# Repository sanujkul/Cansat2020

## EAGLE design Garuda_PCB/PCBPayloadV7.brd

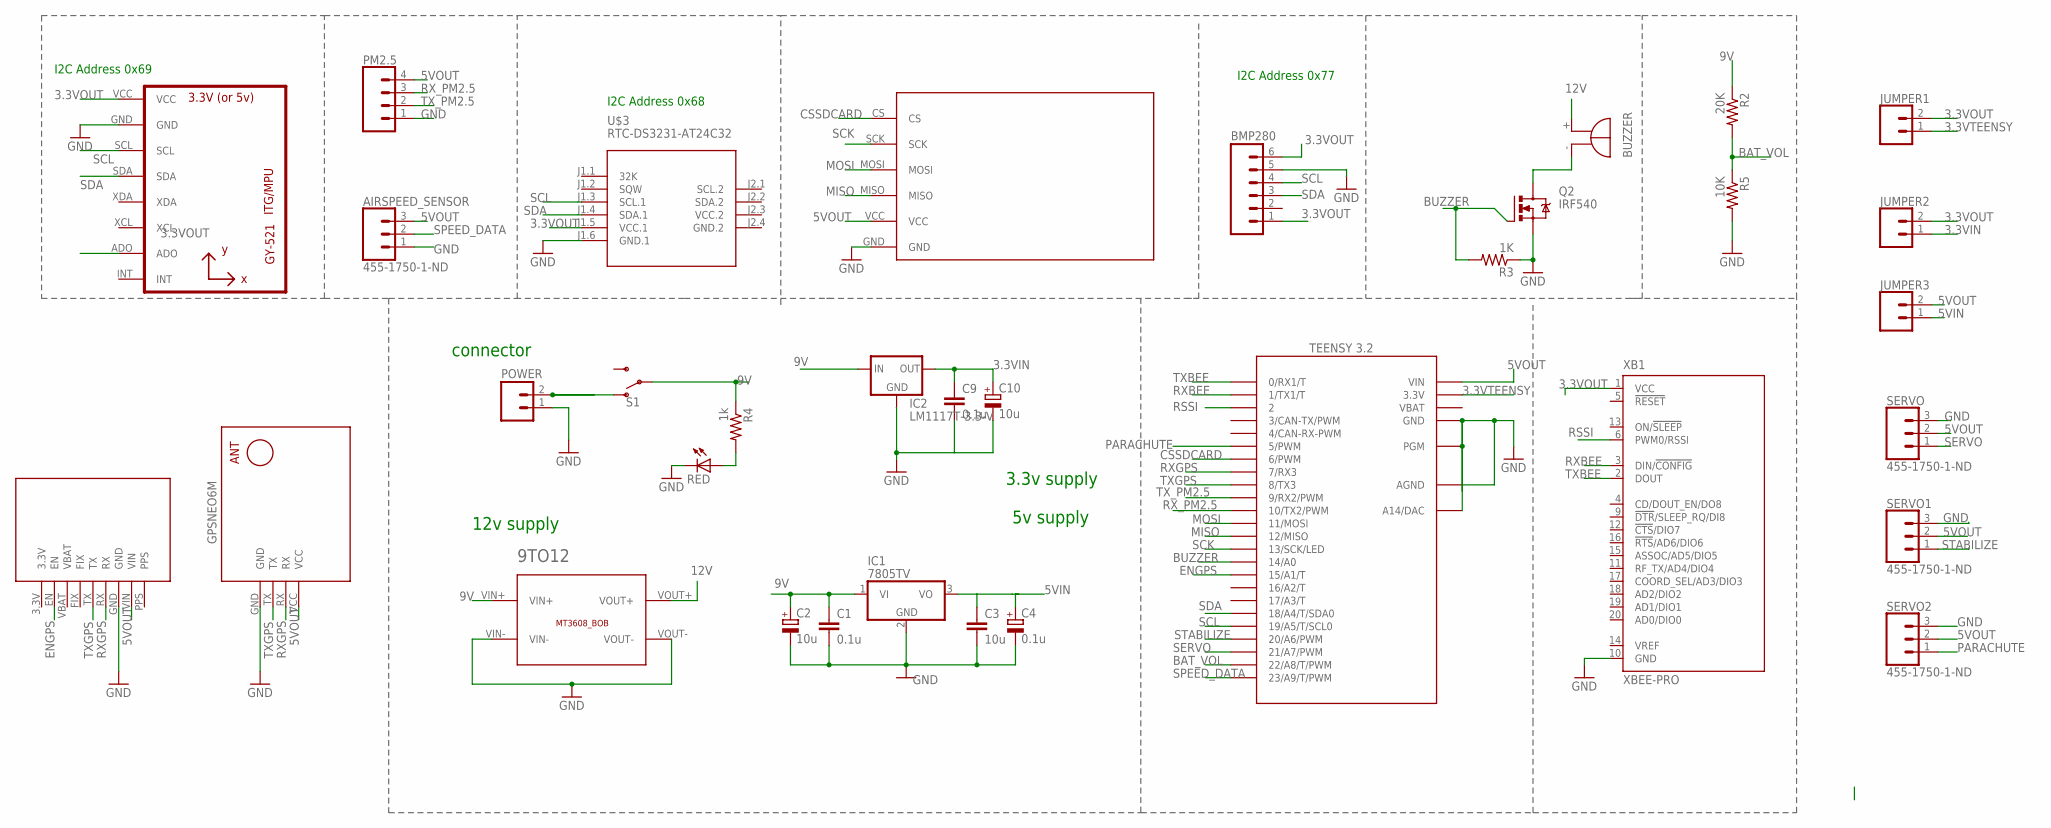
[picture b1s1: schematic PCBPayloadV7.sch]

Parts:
9TO12: BREAKOUTS_MT3608_BOB
AIRSPEED_SENSOR: 455-1750-1-ND; 1X03
BMP280: M06; 06P
C1, C9: 0.1u; C025-025X050
C2, C10: 10u; E2,5-6
C3: 10u; C025-025X050
C4: 0.1u; E2,5-6
IC1: 7805TV; TO220V
IC2: LM1117T-3.3-V; TO220V
JUMPER1, JUMPER2, JUMPER3: CONN_02; 1X02
PM2.5: CONN_04; 1X04
POWER: CEDT_JANUARY_2015_V5_M02; CEDT_JANUARY_2015_V5_02P
Q2: IRF540; TO220BV
R2: 20K; 0204/7
R3: 1K; 0204/7
R4: 1k; 0204/7
R5: 10K; 0204/7
RED: red; LED3MM
S1: SWITCH-SPDT-PTH-11.6X4.0MM; SWITCH_SPDT_PTH_11.6X4.0MM
SERVO, SERVO1, SERVO2: 455-1750-1-ND; 1X03
SG1: BUZZER_EB2209A
U1: GY-521MPU6050; GY-521
U$1: GPS-RECEIVER-NEO6M
U$2: TEENSY_3.1-3.2_OUTER_ROW; TEENSY_3.0-3.2&LC_OUTER_ROW
U$3: RTC-DS3231-AT24C32
U$4: ADAFRUIT_GPS
U$5: SDCARD; M0SDCARDMODULE
XB1: XBEE-PRO

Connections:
3.3VIN: C9.1, C10.+, IC2.2 (OUT), JUMPER2.1
3.3VOUT: BMP280.1, BMP280.6, JUMPER1.2, JUMPER2.2, U1.ADO, U1.VCC, U$3.J1.5 (VCC.1), XB1.1 (VCC)
3.3VTEENSY: JUMPER1.1, U$2.3.3V, U$2.3.3V1 (3.3V)
5VIN: C3.1, C4.+, IC1.3 (VO), JUMPER3.1
5VOUT: AIRSPEED_SENSOR.3, JUMPER3.2, PM2.5.4, SERVO.2, SERVO1.2, SERVO2.2, U$1.VCC, U$2.VIN, U$4.VIN, U$5.VCC
9V: 9TO12.VIN+, C1.1, C2.+, IC1.1 (VI), IC2.3 (IN), R2.1, R4.1, S1.2
12V: 9TO12.VOUT+, SG1.+
BAT_VOL: R2.2, R5.1, U$2.22/A8 (22/A8/T/PWM)
BUZZER: Q2.G, R3.2, U$2.14/A0
CSSDCARD: U$2.6 (6/PWM), U$5.CS
ENGPS: U$2.15/A1 (15/A1/T), U$4.EN
GND: 9TO12.VIN-, 9TO12.VOUT-, AIRSPEED_SENSOR.1, BMP280.5, C1.2, C2.-, C3.2, C4.-, C9.2, C10.-, IC1.2 (GND), IC2.1 (GND), PM2.5.1, POWER.1, Q2.S, R3.1, R5.2, RED.K (C), SERVO.3, SERVO1.3, SERVO2.3, U1.GND, U$1.GND, U$2.AGND, U$2.GND, U$2.GND1 (GND), U$2.PGM, U$2.RESET/DAC (A14/DAC), U$3.J1.6 (GND.1), U$4.GND, U$5.GND, XB1.10 (GND)
GND.2: U$3.J2.4 (GND.2)
MISO: U$2.12 (12/MISO), U$5.MISO
MOSI: U$2.11 (11/MOSI), U$5.MOSI
unnamed: POWER.2, S1.1 (O)
unnamed: R4.2, RED.A
unnamed: Q2.D, SG1.-
PARACHUTE: SERVO2.1, U$2.5 (5/PWM)
RSSI: U$2.2, XB1.6 (PWM0/RSSI)
RXBEE: U$2.1 (1/TX1/T), XB1.3 (DIN/!CONFIG)
RXGPS: U$1.RX, U$2.7 (7/RX3), U$4.RX
RX_PM2.5: PM2.5.3, U$2.10 (10/TX2/PWM)
SCK: U$2.13 (13/SCK/LED), U$5.SCK
SCL: BMP280.4, U1.SCL, U$2.19/A5 (19/A5/T/SCL0), U$3.J1.3 (SCL.1)
SDA: BMP280.3, U1.SDA, U$2.18/A4 (18/A4/T/SDA0), U$3.J1.4 (SDA.1)
SERVO: SERVO.1, U$2.21/A7 (21/A7/PWM)
SPEED_DATA: AIRSPEED_SENSOR.2, U$2.23/A9 (23/A9/T/PWM)
STABILIZE: SERVO1.1, U$2.20/A6 (20/A6/PWM)
TXBEE: U$2.0 (0/RX1/T), XB1.2 (DOUT)
TXGPS: U$1.TX, U$2.8 (8/TX3), U$4.TX
TX_PM2.5: PM2.5.2, U$2.9 (9/RX2/PWM)
VBAT: U$2.VBAT
VCC.2: U$3.J2.3 (VCC.2)

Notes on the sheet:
connector
3.3v supply
5v supply
12v supply
I2C Address 0x77
I2C Address 0x68
I2C Address 0x69

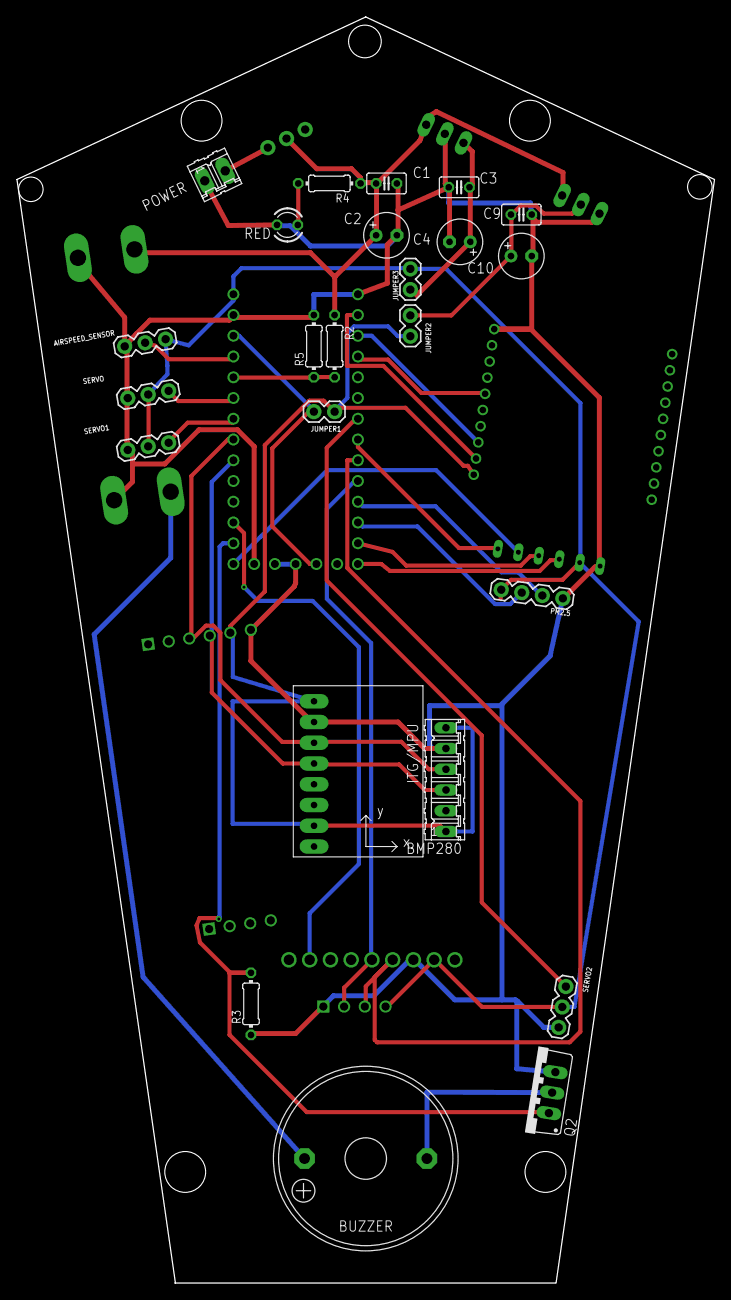
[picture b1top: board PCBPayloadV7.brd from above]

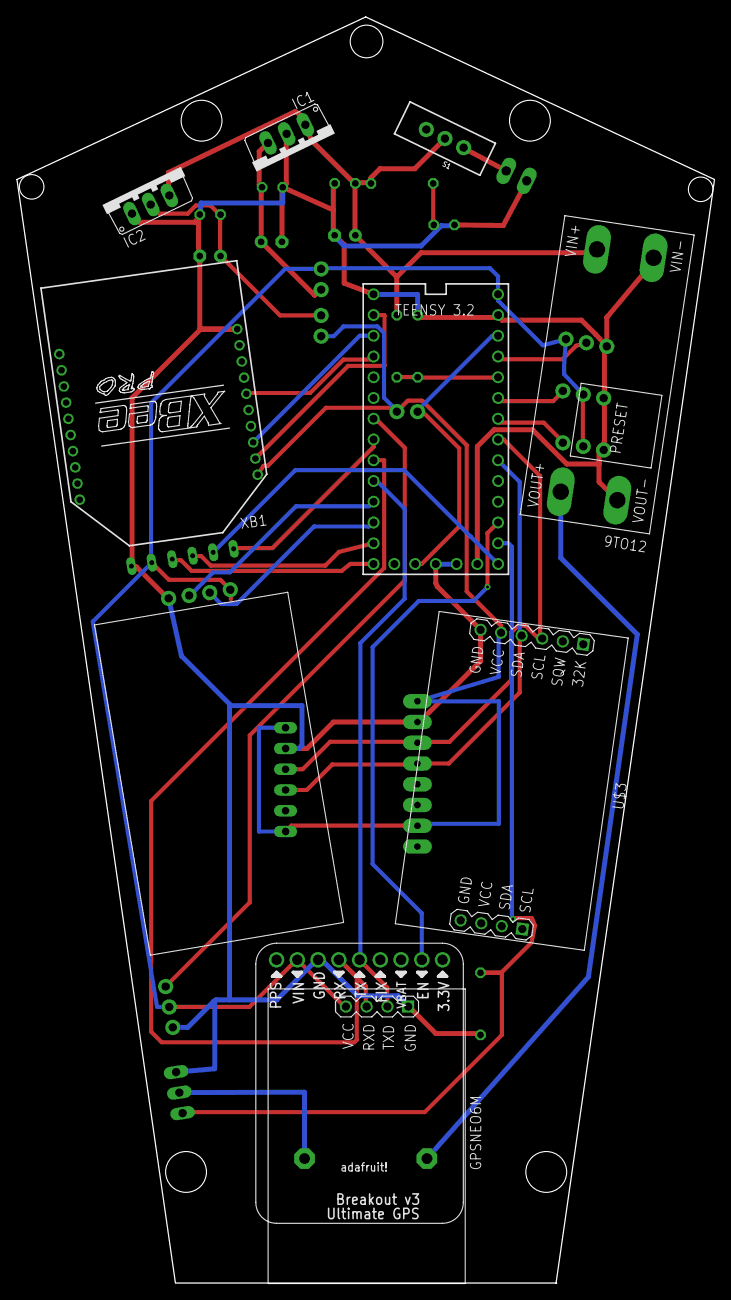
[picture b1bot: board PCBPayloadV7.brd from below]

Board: 2 copper layers, 85.4 x 155.0 mm, 34 parts (10 on the bottom side), 31 nets.

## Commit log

2019-11-02 Made the class for packet for making a packet object and usin it
2019-11-09 Adding pcbs designed for Team KALAM by Sumiran Bhasin
2019-11-09 Completed sch and board layout placement
2019-11-09 routed pcb v03
2019-11-09 routed pcb v04 and added 1 servo for camera stabilization
2019-11-20 Changed dimensions
2019-11-21 Add files via upload
    Drill Holes added, dimensions scaled down for Mech design. Dated 22-nov-2019
2019-11-22 Add files via upload
    Wiring and placement improved
2019-11-22 PCB Version 7 with DXF
    Added DXF File for Mech Team

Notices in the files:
parts and their libraries:
diy-modules: Released under the Creative Commons Attribution 4.0 International License: http://creativecommons.org/licenses/by/4.0
SparkFun-Connectors: Licensing: Creative Commons ShareAlike 4.0 International - https://creativecommons.org/licenses/by-sa/4.0
